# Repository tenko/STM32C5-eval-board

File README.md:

# STM32C5-eval-board

Custom *STM32C5* board in the breadboard friendly *BluePill* format designed in *Kicad v10*.

**Features**

- Compact breadboard friendly board size at 53.5mm x 20mm with 2x16 pin headers.
- STM32C551CE Cortex-M33 MCU, 144 MHz, 512 KB flash, 128 KB RAM. ([Product page](https://www.st.com/en/microcontrollers-microprocessors/stm32c551ce.html) / [Datasheet](https://www.st.com/resource/en/datasheet/stm32c551ce.pdf))
- USB-C power connection with CH340E uart to usb bridge (USART1 used).
- LSE 32768 Hz crystal and HSE with 24 MHz crystal.
- 3V3 LDO with power status led.
- Reset button.
- User led and user button.
- SWD header for programming (Must be used as BOOT0 is not exposed).
- All other MCU pins is routed to board edge headers.

**Note** 

This MCU family is quite new and therefore not all variants of this MCU was available with the usual suppliers
when this board was created. When other variants with *LQFP-48* footprints is available this should be pin compatible
with the layout of this board.

**Pinout** 

For complete pin alternative function definitions it is recommended to use the *STMicroelectronics* application *CubeMX2*.

**Production**

Production files adapted to [PCBWay](https://www.pcbway.com/) recommendations is found in the *fab* folder.

**Firmware**

As this is a new MCU family I could only get the *STMicroelectronics* original software
and hardware to work with flashing the device. *SEGGER's J-Link* Debug Probe will also
probably support this MCU family.

In the *firmware* folder there is a project file for *CubeMX2*. By opening this file
it as matter of generate the *CMake* project files.

I used *VSCode* and the *CubeMX* extension to open the generated *CMake* project files and
added the following test code for a simple blinker application:

```C++
/*
  * You can start your application code here
  */

while (1) {
  printf("hello!\n");
  HAL_GPIO_TogglePin(HAL_GPIOB, HAL_GPIO_PIN_9);
  HAL_Delay(2000);
}
```

**Alternative Firmware in Oberon-2**

As an alternative to *C/C++* the [ECSOberon](https://ecs.openbrace.org/) language and the
[ECSMicroLib](https://github.com/tenko/ECSMicroLib/) framework can be used to develop
firmware for this board.

*ECSOberon* has a number of benefits for MCU applications:

- Simplest possible language (the [language report](https://github.com/OberonSystem3/TheOberonCompanionCD/blob/main/Papers/Oberon2.pdf?raw=true) is 20 pages), yet supporting 
  object oriented design with single inheritance.
- The language has the bit *SET* type which makes fiddling with bit register of the *MCU* very easy and natural.
- The *ECSOberon* language is updated with manual allocation, unsigned types, variable pointers, packages and simple templates.
  Making the language more practical for system programming and *MCUs* than the original *Oberon-2* implementation.
- No header files to worry about. The visibility of the code elements is defined directly in the module.
- The module and package concept keeps the code cleanly segregated and avoid the problem with colliding names in *C*.
- The [documentation](https://ecs.openbrace.org/manual/) is excellent and reported bugs is fixed quickly.

The drawbacks of *ECSOberon*:

- *Oberon-2* is a verbose language and require upper case keyword.
  However with an *IDE* and auto-completion this is a minor issue in my opinion.
- No support for a pre-processor. Some cases can be solved with help of templates, but otherwise
  this must be solved with shell scripts.
  However this omission keeps the code base readable in my opinion.
- Not much existing code exists and many things must be implemented from scratch.
  Code from the original [OberonSystem 3](https://github.com/OberonSystem3) or from [BlackBox Component Builder](https://blackbox.oberon.org/) could be reused.
  
  This is the major drawback in my opinion.

**Testing**

[board-testing.webm](https://github.com/user-attachments/assets/a6211ade-eac5-4887-8b39-223c8f42b538)

The board has been verified to work correctly with the uart-to-usb bridge, leds, buttons and crystals.

Minor issues:

- The *SWDIO* and *SWDCLK* pin was swapped.
- The silkscreen was difficult to read.

This will be fixed in a future revision along with any other issue.

**TODO** 

- Fix *SWD CLK/DIO* swap on silkscreen and schematic.
- Possible expose *BOOT0* with a test point on PCB.
- Possible add PCB jumper to disconnect power led for battery operations.
- Review pins used for user button/led and usb-to-uart.

**Sponsors** 

This board was generously sponsored by [PCBWay](https://www.pcbway.com/) and this project was handled
in quick and professional way in my experience. Thanks.

**Acknowledgments**

This board was developed and with help of and inspiration by the excellent instruction videos on the [Phil's Lab](https://www.youtube.com/@PhilsLab)
Youtube channel.

Also initially skeptical to *KiCAD* software, it turned out to be a very nice experience working with this application.
The team behind *KiCAD* does an excellent job in turning this application into a professional tool.

## License
This project is licensed under the MIT License - see the LICENSE file for details.

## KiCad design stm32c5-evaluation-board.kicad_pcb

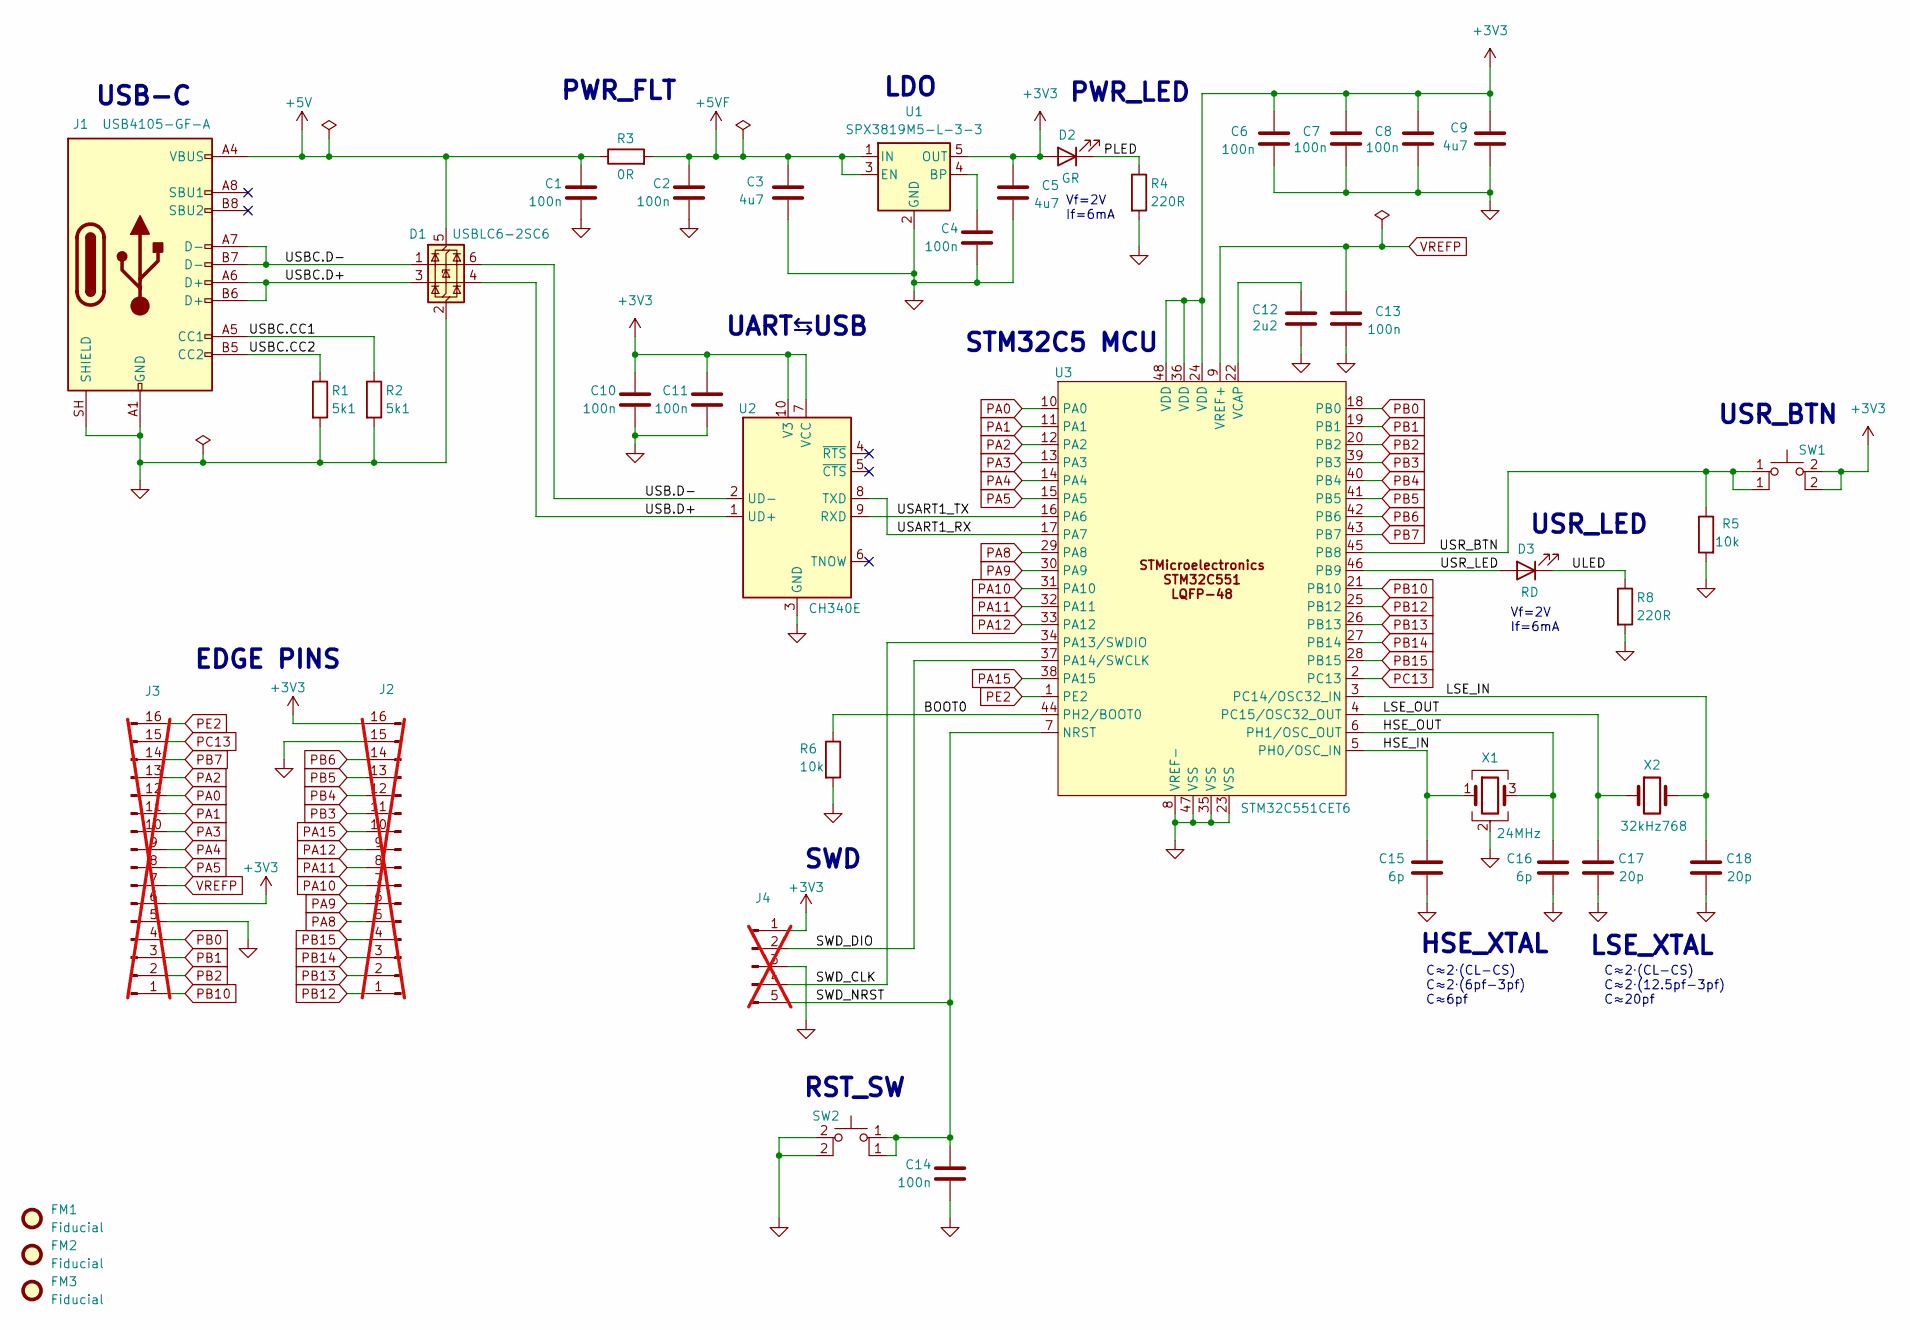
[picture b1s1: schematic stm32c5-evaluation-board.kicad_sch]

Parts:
C1, C2, C4, C6, C7, C8, C10, C11, C13, C14: 100n; C_0402_1005Metric; Manufacturer Part Number GRM155R71E104KE14D
C3, C5, C9: 4u7; C_0805_2012Metric; Manufacturer Part Number GRM21BZ71E475KE15L
C12: 2u2; C_0603_1608Metric; Manufacturer Part Number GRM188Z71E225KE43D
C15, C16: 6p; C_0402_1005Metric; Manufacturer Part Number GCM1555C1H6R0BA16D
C17, C18: 20p; C_0402_1005Metric; Manufacturer Part Number GCM1555C1H200FA16D
D1: USBLC6-2SC6; SOT-23-6; Manufacturer Part Number USBLC6-2SC6
D2: GR; LED_0402_1005Metric; Manufacturer Part Number 150040VS73240
D3: RD; LED_0402_1005Metric; Manufacturer Part Number 150040RS73240
FM1, FM2, FM3: Fiducial; Fiducial_1mm_Mask2mm
J1: USB4105-GF-A; USB_C_Receptacle_GCT_USB4105-xx-A_16P_TopMnt_Horizontal; Manufacturer Part Number USB4105-GF-A-120
J2, J3: Conn_01x16_Pin; PinHeader_1x16_P2.54mm_Vertical; not fitted
J4: Conn_01x05_Pin; PinHeader_1x05_P2.54mm_Horizontal; not fitted
R1, R2: 5k1; R_0402_1005Metric; Manufacturer Part Number RC0402FR-075K1L
R3: 0R; R_0402_1005Metric; Manufacturer Part Number RC0402FR-070RL
R4, R8: 220R; R_0402_1005Metric; Manufacturer Part Number RC0402FR-07220RL
R5, R6: 10k; R_0402_1005Metric; Manufacturer Part Number RC0402FR-0710KL
SW1, SW2: EVQ-P2K02Q; SW_SPST_EVQP2_MiddlePushTravel_H2.5mm; Manufacturer Part Number EVQ-P2K02Q
U1: SPX3819M5-L-3-3; SOT-23-5; Manufacturer Part Number SPX3819M5-L-3-3
U2: CH340E; MSOP-10_3x3mm_P0.5mm; Manufacturer Part Number CH340E
U3: STM32C551CET6; LQFP-48_7x7mm_P0.5mm; Manufacturer Part Number STM32C551CET6
X1: 24MHz; Crystal_SMD_2016-4Pin_2.0x1.6mm; Manufacturer Part Number CX2016FB24000B0FZZH1
X2: 32kHz768; Crystal_SMD_3215-2Pin_3.2x1.5mm; Manufacturer Part Number FC-135 32.7680KA-A3

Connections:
+3V3: C5.1, C6.1, C7.1, C8.1, C9.1, C10.1, C11.1, D2.2 (A), J2.16, J3.6, J4.1, SW1.2 (C), U1.5 (OUT), U2.7 (VCC), U2.10 (V3), U3.24 (VDD), U3.36 (VDD), U3.48 (VDD)
+5V: C1.1, D1.5 (VBUS), J1.A4 (VBUS), J1.A9 (VBUS), J1.B4 (VBUS), J1.B9 (VBUS), R3.1
+5VF: C2.1, C3.1, R3.2, U1.1 (IN), U1.3 (EN)
/BOOT0: R6.1, U3.44 (PH2/BOOT0)
/HSE_IN: C15.1, U3.5 (PH0/OSC_IN), X1.1
/HSE_OUT: C16.1, U3.6 (PH1/OSC_OUT), X1.3
/LSE_IN: C18.1, U3.3 (PC14/OSC32_IN), X2.2
/LSE_OUT: C17.1, U3.4 (PC15/OSC32_OUT), X2.1
/PLED: D2.1 (K), R4.1
/SWD_CLK: J4.4, U3.34 (PA13/SWDIO)
/SWD_DIO: J4.2, U3.37 (PA14/SWCLK)
/SWD_NRST: C14.1, J4.5, SW2.1 (A), U3.7 (NRST)
/ULED: D3.1 (K), R8.1
/USART1_RX: U2.8 (TXD), U3.17 (PA7)
/USART1_TX: U2.9 (RXD), U3.16 (PA6)
/USB.D+: D1.4 (I/O2), U2.1 (UD+)
/USB.D-: D1.6 (I/O1), U2.2 (UD-)
/USBC.CC1: J1.A5 (CC1), R2.1
/USBC.CC2: J1.B5 (CC2), R1.1
/USBC.D+: D1.3 (I/O2), J1.A6 (D+), J1.B6 (D+)
/USBC.D-: D1.1 (I/O1), J1.A7 (D-), J1.B7 (D-)
/USR_BTN: R5.1, SW1.1 (A), U3.45 (PB8)
/USR_LED: D3.2 (A), U3.46 (PB9)
GND: C1.2, C2.2, C3.2, C4.2, C5.2, C6.2, C7.2, C8.2, C9.2, C10.2, C11.2, C12.1, C13.2, C14.2, C15.2, C16.2, C17.2, C18.2, D1.2 (GND), J1.A1 (GND), J1.A12 (GND), J1.B1 (GND), J1.B12 (GND), J1.SH (SHIELD), J2.15, J3.5, J4.3, R1.2, R2.2, R4.2, R5.2, R6.2, R8.2, SW2.2 (D), U1.2 (GND), U2.3 (GND), U3.8 (VREF-), U3.23 (VSS), U3.35 (VSS), U3.47 (VSS), X1.2 (G), X1.4 (G)
unnamed: C4.1, U1.4 (BP)
unnamed: C12.2, U3.22 (VCAP)
PA0: J3.12, U3.10 (PA0)
PA1: J3.11, U3.11 (PA1)
PA2: J3.13, U3.12 (PA2)
PA3: J3.10, U3.13 (PA3)
PA4: J3.9, U3.14 (PA4)
PA5: J3.8, U3.15 (PA5)
PA8: J2.5, U3.29 (PA8)
PA9: J2.6, U3.30 (PA9)
PA10: J2.7, U3.31 (PA10)
PA11: J2.8, U3.32 (PA11)
PA12: J2.9, U3.33 (PA12)
PA15: J2.10, U3.38 (PA15)
PB0: J3.4, U3.18 (PB0)
PB1: J3.3, U3.19 (PB1)
PB2: J3.2, U3.20 (PB2)
PB3: J2.11, U3.39 (PB3)
PB4: J2.12, U3.40 (PB4)
PB5: J2.13, U3.41 (PB5)
PB6: J2.14, U3.42 (PB6)
PB7: J3.14, U3.43 (PB7)
PB10: J3.1, U3.21 (PB10)
PB12: J2.1, U3.25 (PB12)
PB13: J2.2, U3.26 (PB13)
PB14: J2.3, U3.27 (PB14)
PB15: J2.4, U3.28 (PB15)
PC13: J3.15, U3.2 (PC13)
PE2: J3.16, U3.1 (PE2)
VREFP: C13.1, J3.7, U3.9 (VREF+)

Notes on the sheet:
SWD
USR_LED
USB-C
EDGE PINS
PWR_FLT
STM32C5 MCU
RST_SW
USR_BTN
Vf=2V If=6mA
UART⇆USB
C≈2⋅(CL-CS) C≈2⋅(12.5pf-3pf) C≈20pf
LSE_XTAL
LDO
HSE_XTAL
C≈2⋅(CL-CS) C≈2⋅(6pf-3pf) C≈6pf
PWR_LED

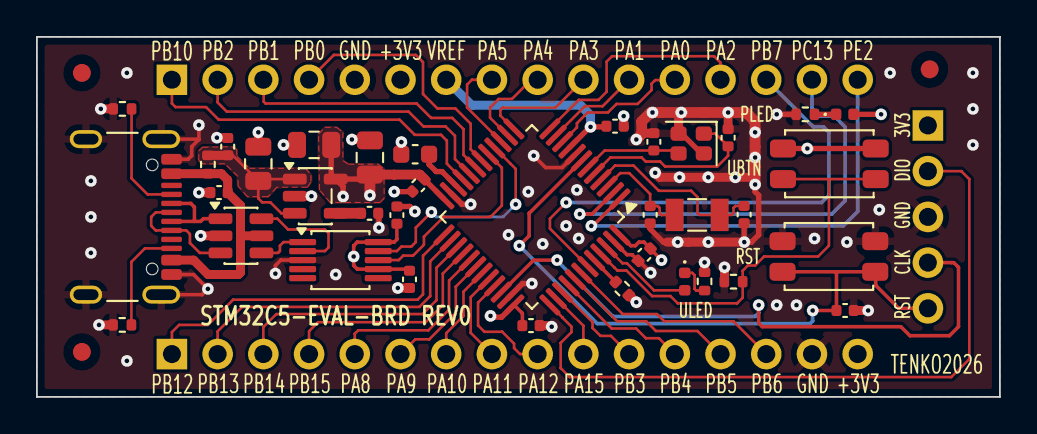
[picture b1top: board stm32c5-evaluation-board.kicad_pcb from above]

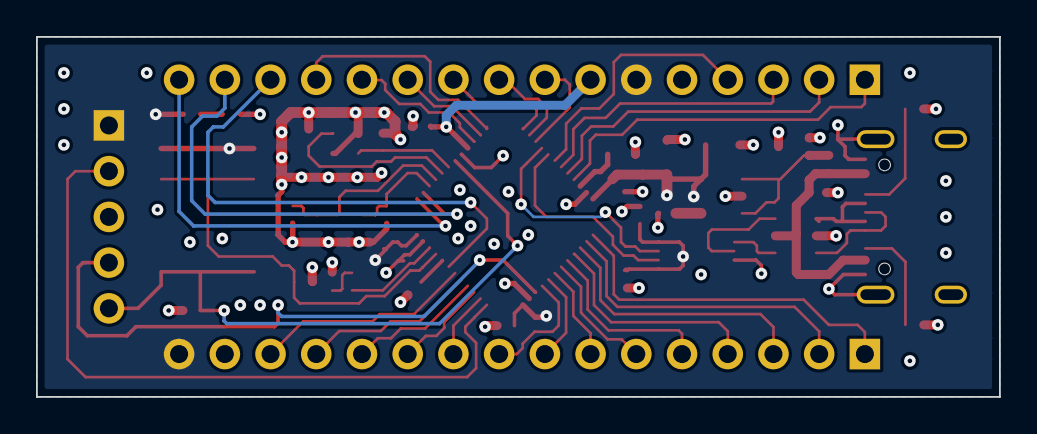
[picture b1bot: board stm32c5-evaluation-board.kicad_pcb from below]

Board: 4 copper layers, 53.5 x 20.0 mm, 42 parts (2 on the bottom side), 54 nets.

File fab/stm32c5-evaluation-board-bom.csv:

Item #,Designator,Qty,Manufacturer,Mfg Part #,Description,Value,Footprint,Datasheet,Distributor Link 1,Distributor Link 2
1,"C1,C2,C4,C6,C7,C8,C10,C11,C13,C14",10,Murata Electronics,GRM155R71E104KE14D,Unpolarized capacitor MLCC X7R,100n,Capacitor_SMD:C_0402_1005Metric,https://search.murata.co.jp/Ceramy/image/img/A01X/G101/ENG/G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,https://eu.mouser.com/ProductDetail/Murata-Electronics/GRM15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,https://www.digikey.com/en/products/detail/murata-electronic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
2,"C3,C5,C9",3,Murata Electronics,GRM21BZ71E475KE15L,Unpolarized capacitor MLCC X7R,4u7,Capacitor_SMD:C_0805_2012Metric,https://search.murata.co.jp/Ceramy/image/img/A01X/G101/ENG/G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,https://eu.mouser.com/ProductDetail/Murata-Electronics/GRM21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,https://www.digikey.com/en/products/detail/murata-electronic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
3,C12,1,Murata Electronics ,GRM188Z71E225KE43D,Unpolarized capacitor MLCC X7R,2u2,Capacitor_SMD:C_0603_1608Metric,https://pim.murata.com/asset/pim4/ceramicCapacitorSMD/GRM188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,https://eu.mouser.com/ProductDetail/Murata-Electronics/GRM18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,https://www.digikey.com/en/products/detail/murata-electronic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
4,"C15,C16",2,Murata Electronics ,GCM1555C1H6R0BA16D ,Unpolarized capacitor MLCC NP0,6p,Capacitor_SMD:C_0402_1005Metric,https://eu.mouser.com/datasheet/3/76/3/GCM1555C1H6R0BA16_01A.pdf,https://eu.mouser.com/ProductDetail/Murata-Electronics/GCM15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,https://www.digikey.com/en/products/detail/murata-electronic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
5,"C17,C18",2,Murata Electronics ,GCM1555C1H200FA16D,Unpolarized capacitor MLCC NP0,20p,Capacitor_SMD:C_0402_1005Metric,https://pim.murata.com/asset/pim4/ceramicCapacitorSMD/GCM155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,https://eu.mouser.com/ProductDetail/Murata-Electronics/GCM15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,https://www.digikey.com/en/products/detail/murata-electronic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
6,D1,1, STMicroelectronics,USBLC6-2SC6,"Very low capacitance ESD protection diode, 2 data-line, SOT-23-6",USBLC6-2SC6,Package_TO_SOT_SMD:SOT-23-6,https://www.st.com/resource/en/datasheet/usblc6-2.pdf,https://www.digikey.com/en/products/detail/stmicroelectronic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,https://eu.mouser.com/ProductDetail/STMicroelectronics/USBLC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
7,D2,1,Wurth Elektronik ,150040VS73240 ,Light emitting diode green,GR,LED_SMD:LED_0402_1005Metric,https://www.we-online.com/components/products/datasheet/1500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,https://eu.mouser.com/ProductDetail/Wurth-Elektronik/150040V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,https://www.digikey.com/en/products/detail/w%C3%BCrth-elektr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
8,D3,1,Wurth Elektronik ,150040RS73240,Light emitting diode,RD,LED_SMD:LED_0402_1005Metric,https://www.we-online.com/components/products/datasheet/1500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,https://eu.mouser.com/ProductDetail/Wurth-Elektronik/150040R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,https://www.digikey.com/en/products/detail/w%C3%BCrth-elektr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
9,J1,1,Global Connector Technology ,USB4105-GF-A-120 ,USB 2.0-only 16P Type-C Receptacle connector,USB4105-GF-A,Connector_USB:USB_C_Receptacle_GCT_USB4105-xx-A_16P_TopMnt_Horizontal,https://www.mouser.com/catalog/specsheets/Global_Connector_T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,https://eu.mouser.com/ProductDetail/GCT/USB4105-GF-A-120?qs=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,https://www.digikey.com/en/products/detail/gct/USB4105-GF-A-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
10,"R1,R2",2,YAGEO,RC0402FR-075K1L,Resistor,5k1,Resistor_SMD:R_0402_1005Metric,https://www.mouser.com/catalog/specsheets/YAGEO_PYu_RC_Group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,https://eu.mouser.com/ProductDetail/YAGEO/RC0402FR-075K1L?qs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,https://www.digikey.com/en/products/detail/yageo/RC0402FR-07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
11,R3,1,YAGEO,RC0402FR-070RL ,Resistor,0R,Resistor_SMD:R_0402_1005Metric,https://www.mouser.com/catalog/specsheets/YAGEO_PYu_RC_Group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,https://eu.mouser.com/ProductDetail/YAGEO/RC0402FR-070RL?qs=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,https://www.digikey.com/en/products/detail/yageo/RC0402FR-07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
12,"R4,R8",2,YAGEO,RC0402FR-07220RL,Resistor,220R,Resistor_SMD:R_0402_1005Metric,https://www.mouser.com/catalog/specsheets/YAGEO_PYu_RC_Group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,https://eu.mouser.com/ProductDetail/YAGEO/RC0402FR-07220RL?q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,https://www.digikey.com/en/products/detail/yageo/RC0402FR-07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
13,"R5,R6",2,YAGEO,RC0402FR-0710KL ,Resistor,10k,Resistor_SMD:R_0402_1005Metric,https://www.mouser.com/catalog/specsheets/YAGEO_PYu_RC_Group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,https://eu.mouser.com/ProductDetail/YAGEO/RC0402FR-0710KL?qs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,https://www.digikey.com/en/products/detail/yageo/RC0402FR-07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
14,"SW1,SW2",2, Panasonic,EVQ-P2K02Q,Tactile Switches NO SPST 4.7mm x 3.5mm,EVQ-P2K02Q,Button_Switch_SMD:SW_SPST_EVQP2_MiddlePushTravel_H2.5mm,https://4donline.ihs.com/images/VipMasterIC/IC/PANA/PANAS386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,https://eu.mouser.com/ProductDetail/Panasonic/EVQ-P2K02Q?qs=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,https://www.digikey.com/en/products/detail/panasonic-industr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
15,U1,1,"  MaxLinear, Inc.", SPX3819M5-L-3-3,"500mA Low drop-out regulator, Fixed Output 3.3V, SOT-23-5",SPX3819M5-L-3-3,Package_TO_SOT_SMD:SOT-23-5,https://www.maxlinear.com/Document/index?id=22106&languageid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,https://www.digikey.com/en/products/detail/maxlinear-inc/SPX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,https://eu.mouser.com/ProductDetail/MaxLinear/SPX3819M5-L-3-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
16,U2,1,WCH,CH340E,"USB serial converter, UART, MSOP-10",CH340E,Package_SO:MSOP-10_3x3mm_P0.5mm,https://www.mpja.com/download/35227cpdata.pdf,https://www.lcsc.com/product-detail/C99652.html,
17,U3,1,STMicroelectronics,STM32C551CET6,Microcontroller ARM Cortex-M33 144MHz 512kB 128kB,STM32C551CET6,Package_QFP:LQFP-48_7x7mm_P0.5mm,https://www.st.com/resource/en/datasheet/stm32c551ce.pdf,https://eu.mouser.com/ProductDetail/STMicroelectronics/STM32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,https://www.digikey.com/en/products/detail/stmicroelectronic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
18,X1,1,KYOCERA AVX,CX2016FB24000B0FZZH1 ,"Four pin crystal, GND on pins 2 and 4",24MHz,Crystal:Crystal_SMD_2016-4Pin_2.0x1.6mm,https://ele.kyocera.com/assets/products/crystal-device/speci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,https://eu.mouser.com/ProductDetail/KYOCERA-AVX/CX2016FB2400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,https://www.digikey.com/en/products/detail/kyocera-avx/CX201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
19,X2,1,Epson,FC-135 32.7680KA-A3,Two pin crystal,32kHz768,stm32c5-evaluation-board-footprints:Crystal_SMD_3215-2Pin_3.2x1.5mm,https://download.epsondevice.com/td/pdf/brief/FC-135_en.pdf,https://eu.mouser.com/ProductDetail/Epson-Timing/FC-135R-32.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,https://www.digikey.com/en/products/detail/epson/FC-135-32-7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
